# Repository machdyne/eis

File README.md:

# Eis Computer

Eis is a small FPGA computer designed by Lone Dynamics Corporation.

This repo contains schematics, PCB layouts, pinouts, example firmware, gateware, documentation and a 3D printable case.

Find more information on the [Eis product page](https://machdyne.com/product/eis-computer/).

## Blinky 

Building the blinky example requires [Yosys](https://github.com/YosysHQ/yosys), [nextpnr-ice40](https://github.com/YosysHQ/nextpnr) and [IceStorm](https://github.com/YosysHQ/icestorm).

Assuming they are installed, you can simply type `make` to build the gateware, which will be written to output/blinky.bin. You can then connect the USB-C port to your computer and use the latest version of [ldprog](https://github.com/machdyne/ldprog) to write the gateware to the device.

## Programming

The RP2040 firmware, FPGA SRAM and flash MMOD can be programmed over the USB-C port.

Configure the FPGA SRAM:

```
$ ldprog -i -s blinky.bin
```

Program the flash MMOD:

```
$ ldprog -i -f blinky.bin
```

## Firmware

Eis ships with RP2040 [firmware](firmware) based on the [Müsli](https://github.com/machdyne/musli) firmware which allows it to communicate with [ldprog](https://github.com/machdyne/ldprog).

The firmware is responsible for initializing the system, [configuring and outputting the system clock](https://raspberrypi.github.io/pico-sdk-doxygen/group__hardware__clocks.html#details), and either configuring the FPGA or telling the FPGA to configure itself from the MMOD.

The system clock (CLK\_RP) is 48MHz by default.

The firmware can be updated by holding down the BOOTSEL button, connecting the USB-C port to your computer, and then dragging and dropping a new UF2 file to the device filesystem.

The firmware can be built from source or you can use the latest `eis.uf2` binary from the firmware directory.

## SOC

[Zucker](https://github.com/machdyne/zucker) is an experimental RISC-V SOC that supports Eis.

## Pinouts

 * [MMOD](https://github.com/machdyne/mmod)
 * [DDMI](https://github.com/machdyne/ddmi)

## License

The contents of this repo are released under the [Lone Dynamics Open License](LICENSE.md) with the following exceptions:

- The KiCad design files contain parts of the [kicad-pmod](https://github.com/mithro/kicad-pmod) library which is released under the [Apache License, Version 2.0](https://www.apache.org/licenses/LICENSE-2.0.html).

- The KiCad design files may contain symbols and footprints released under other licenses; please contact us if we've failed to give proper attribution.

Note: You can use these designs for commercial purposes but we ask that instead of producing exact clones, that you either replace our trademarks and logos with your own or add your own next to ours.

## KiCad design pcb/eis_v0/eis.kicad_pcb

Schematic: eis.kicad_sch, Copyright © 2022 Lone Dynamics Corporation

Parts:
C1, C43: 1uF; C_0603_1608Metric
C2, C4, C6, C11, C12, C13, C17, C18: 100nF; C_0603_1608Metric
C3, C5, C8, C9: 220nF; C_0603_1608Metric
C7, C16: 4.7uF; C_0603_1608Metric
C10: 10nF; C_0603_1608Metric
C14, C15: 10uF; C_0603_1608Metric
C19, C20, C21, C23: 100nF; R_0603_1608Metric
C22: 1uF; R_0603_1608Metric
C24, C25: 15pF; C_0402_1005Metric
C26, C34, C40: 1uF; C_0402_1005Metric
C27, C28, C29, C30, C31, C32, C33, C35, C36, C39: 100nF; C_0402_1005Metric
C37: 10uF; R_0402_1005Metric
C38: 100nF; R_0402_1005Metric
C41, C42, C44, C46, C47, C48: 22uF; C_0603_1608Metric
C45: 4.7uF; R_0603_1608Metric
D1: D_Schottky_Small; D_0603_1608Metric
D2: LED; LED_0603_1608Metric
FB1, FB2: Ferrite_Bead; R_0603_1608Metric
H1, H2, H3, H4: MountingHole_Pad; MountingHole_3.2mm_M3_Pad
J1: TYPE-C-31-M-12-FIXED; USB_C_Receptacle_HRO_TYPE-C-31-M-12; PARTREV A
J2: USB_A; USB_A_Stewart_SS-52100-001_Horizontal
J3: MICROSD; SDCARD
J4: Conn_01x02_Male; PinHeader_1x02_P2.54mm_Vertical
J5: HDMI_TE_1827059-3-FIXED
L1, L2: 1uH; L_0603_1608Metric
MMOD1: PMOD-Device-x1-Type-2-SPI; PinSocket_1x06_P2.54mm_Horizontal
PMOD1: PMOD-Device-x2-Type-1A-GPIO; PMOD_2x06_HOST
R1, R8: 5K1; R_0603_1608Metric
R2, R3: 27R; R_0402_1005Metric
R4, R5, R18, R19, R20: 20K; R_0402_1005Metric
R6, R7, R9, R16: 10K; R_0402_1005Metric
R10, R11: 100R; R_0603_1608Metric
R12, R13: 22R; R_0402_1005Metric
R14: 536R; R_0603_1608Metric
R15: 1K; R_0402_1005Metric
R17: 1K; R_0603_1608Metric
R21, R22, R23, R24, R25, R26, R27, R28: 270R; R_0402_1005Metric
R29: 210K; R_0603_1608Metric
R30: 47K; R_0603_1608Metric
R31, R32: 200K; R_0603_1608Metric
SW1: BOOT; Button_2P_3x4mm
TP1: TP_PWR5V0; TestPoint_THTPad_D1.0mm_Drill0.5mm
TP2, TP3, TP4, TP5, TP6, TP7, TP8, TP9: TestPoint; TestPoint_Pad_1.0x1.0mm
TP10: TP_PWR1V8; TestPoint_THTPad_D1.0mm_Drill0.5mm
TP11, TP12: TestPoint; TestPoint_THTPad_D1.0mm_Drill0.5mm
U1: ICE40HX4K-BG121; BGA-121_9.0x9.0mm_Layout11x11_P0.8mm_Ball0.4mm_Pad0.35mm_NS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
U2: APS256; APS256_BGA_24
U3: IS61WV256; BGA48C75P8X6_800X600X120N
U4: RP2040; RP2040-QFN-56-OFFICIAL; PARTREV 1.6.1
U5: W25Q32JVSS; SOIC-8_3.9x4.9mm_P1.27mm
U6: NCP164ASN180T1G; TSOP-5_1.65x3.05mm_P0.95mm
U7, U8: AP61300Z6-7; SOT-563
Y1: ECS-80-12-33-JGN-TR-12MHZ; XTAL_ECS-240-8-33-AGN-TR

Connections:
/BOOT: R17.1, SW1.1
/CDONE: R7.1, U1.K8 (CDONE), U4.5 (GPIO3)
/CRESET: R9.1, U1.L9 (~CRESET), U4.4 (GPIO2)
/CSPI_SCK: J3.5 (CLK), MMOD1.3 (MISO), R6.1, U1.L10 (IOB_107_SCK), U4.38 (GPIO26/ADC0)
/CSPI_SI: J3.7 (DAT0), MMOD1.4 (SCK), R5.1, U1.J9 (IOB_106_SDI), U4.39 (GPIO27/ADC1)
/CSPI_SO: J3.3 (CMD), MMOD1.5 (GND), R4.1, U1.K9 (IOB_105_SDO), U4.36 (GPIO24)
/CSPI_SS: MMOD1.6 (VCC), U1.K10 (IOB_108_SS), U4.34 (GPIO22)
/DDMIC_CK_N: J5.12 (CK-), R28.2
/DDMIC_CK_P: J5.10 (CK+), R27.2
/DDMIC_D0_N: J5.9 (D0-), R26.2
/DDMIC_D0_P: J5.7 (D0+), R25.2
/DDMIC_D1_N: J5.6 (D1-), R24.2
/DDMIC_D1_P: J5.4 (D1+), R23.2
/DDMIC_D2_N: J5.3 (D2-), R22.2
/DDMIC_D2_P: J5.1 (D2+), R21.2
/DDMI_CK_N: R28.1, U1.G1 (IOL_14A_GBIN6)
/DDMI_CK_P: R27.1, U1.G2 (IOL_14B)
/DDMI_D0_N: R26.1, U1.H1 (IOL_18A)
/DDMI_D0_P: R25.1, U1.H2 (IOL_18B)
/DDMI_D1_N: R24.1, U1.J1 (IOL_23A)
/DDMI_D1_P: R23.1, U1.J2 (IOL_25B)
/DDMI_D2_N: R22.1, U1.K1 (IOL_23B)
/DDMI_D2_P: R21.1, U1.K2 (IOL_25A)
/HRAM_ADQ0: U1.J11 (IOR_114), U2.D3 (ADQ0)
/HRAM_ADQ1: U1.G10 (IOR_120), U2.D2 (ADQ1)
/HRAM_ADQ2: U1.G9 (IOR_128), U2.C4 (ADQ2)
/HRAM_ADQ3: U1.H10 (IOR_116), U2.D4 (ADQ3)
/HRAM_ADQ4: U1.F9 (IOR_137), U2.D5 (ADQ4)
/HRAM_ADQ5: U1.K11 (IOR_115), U2.E3 (ADQ5)
/HRAM_ADQ6: U1.J10 (IOR_117), U2.E2 (ADQ6)
/HRAM_ADQ7: U1.G11 (IOR_129), U2.E1 (ADQ7)
/HRAM_CE: U1.D10 (IOR_154), U2.A3 (CE#)
/HRAM_CK: U1.E10 (IOR_141_GBIN2), U2.B2 (CK)
/HRAM_DQ8: U1.F10 (IOR_136), U2.C2 (DQ8)
/HRAM_DQ9: U1.E11 (IOR_148), U2.B1 (DQ9)
/HRAM_DQ10: U1.D11 (IOR_152), U2.A2 (DQ10)
/HRAM_DQ11: U1.C11 (IOR_160), U2.A4 (DQ11)
/HRAM_DQ12: U1.B11 (IOR_161), U2.A5 (DQ12)
/HRAM_DQ13: U1.E8 (IOR_146), U2.B4 (DQ13)
/HRAM_DQ14: U1.D9 (IOR_147), U2.B5 (DQ14)
/HRAM_DQ15: U1.H11 (IOR_119), U2.C5 (DQ15)
/HRAM_DQS0: U1.F11 (IOR_140_GBIN3), U2.C3 (DQSDM0)
/HRAM_DQS1: U1.E9 (IOR_144), U2.B3 (DQSDM1)
/LED: R14.1, U1.G3 (IOL_17A)
/PMOD_A1: PMOD1.1 (IOA0), U1.L4 (IOB_72)
/PMOD_A2: PMOD1.2 (IOA1), U1.L1 (IOB_56)
/PMOD_A3: PMOD1.3 (IOA2), U1.K3 (IOB_63)
/PMOD_A4: PMOD1.4 (IOA3), U1.J4 (IOB_64)
/PMOD_A7: PMOD1.7 (IOB0), U1.L3 (IOB_71)
/PMOD_A8: PMOD1.8 (IOB1), U1.K5 (IOB_79)
/PMOD_A9: PMOD1.9 (IOB2), U1.K4 (IOB_73)
/PMOD_A10: PMOD1.10 (IOB3), U1.J3 (IOB_57)
/PWR1V1: C30.1, C32.1, C34.1, U4.23 (DVDD), U4.45 (VREG_VOUT), U4.50 (DVDD)
/PWR1V2: C1.1, C3.1, C5.1, C8.1, C9.1, C10.1, C44.1, C48.1, L2.2, R10.1, R11.1, R31.1, TP12.1, U1.D4 (VCC), U1.D8 (VCC), U1.H4 (VCC), U1.H8 (VCC), U7.5 (EN), U8.6 (OUT)
/PWR1V8: C11.1, C19.2, C20.2, C45.2, TP10.1, U1.F8 (VCCIO_1), U2.D1 (VDD), U2.E4 (VDD1), U6.5 (OUT)
/PWR2V5: C6.1, D1.1 (K), U1.C10 (VPP_2V5)
/PWR3V3: C2.1, C4.1, C17.1, C18.1, C21.2, C22.2, C23.2, C26.1, C27.1, C28.1, C29.1, C31.1, C33.1, C35.1, C36.1, C37.1, C38.1, C39.1, C40.1, C43.1, C46.1, C47.1, D1.2 (A), D2.2 (A), J3.4 (VDD), L1.2, MMOD1.1 (SS), PMOD1.6 (VCC), PMOD1.12 (VCC), R4.2, R5.2, R6.2, R7.2, R9.2, R16.1, R18.1, R19.1, R20.1, R29.1, TP11.1, U1.D6 (VCCIO_0), U1.E4 (VCCIO_3), U1.G4 (VCCIO_3), U1.H6 (VCCIO_2), U1.L11 (VCC_SPI), U3.D6 (VDD2), U3.E1 (VDD1), U4.1 (IOVDD), U4.10 (IOVDD), U4.22 (IOVDD), U4.26 (RUN), U4.33 (IOVDD), U4.42 (IOVDD), U4.43 (ADC_AVDD), U4.44 (VREG_VIN), U4.48 (USB_VDD), U4.49 (IOVDD), U5.8 (VCC), U6.1 (IN), U6.3 (EN), U7.6 (OUT)
/PWR5V0: C7.1, C16.1, C41.1, C42.1, FB1.1, FB2.1, J4.1, J5.18 (+5V), TP1.1, U7.3 (VIN), U8.3 (VIN), U8.5 (EN)
/RP_CLK: U1.L5 (IOB_81_GBIN5), U4.35 (GPIO23)
/RP_INT: U1.K7 (IOB_89), U4.29 (GPIO18)
/RP_QSPI_IO0: TP3.1, U4.53 (QSPI_SD0), U5.5 (DI(IO0))
/RP_QSPI_IO1: TP4.1, U4.55 (QSPI_SD1), U5.2 (DO(IO1))
/RP_QSPI_IO2: TP5.1, U4.54 (QSPI_SD2), U5.3 (IO2)
/RP_QSPI_IO3: TP6.1, U4.51 (QSPI_SD3), U5.7 (IO3)
/RP_QSPI_SCK: TP7.1, U4.52 (QSPI_SCLK), U5.6 (CLK)
/RP_QSPI_SS: R16.2, R17.2, TP2.1, U4.56 (QSPI_CSN), U5.1 (~CS)
/RP_RX: U1.L8 (IOB_103_CBSEL0), U4.28 (GPIO17)
/RP_SS: U1.J7 (IOB_86), U4.37 (GPIO25)
/RP_TX: U1.L7 (IOB_94), U4.27 (GPIO16)
/SD_DAT1: J3.8 (DAT1), R20.2
/SD_DAT2: J3.1 (DAT2), R19.2
/SD_SS: J3.2 (DAT3/CD), R18.2, U1.J8 (IOB_91), U4.7 (GPIO5)
/SRAM_A0: U1.C1 (IOL_5B), U3.A3 (A0)
/SRAM_A1: U1.D1 (IOL_8B), U3.A4 (A1)
/SRAM_A2: U1.E1 (IOL_8A), U3.A5 (A2)
/SRAM_A3: U1.C2 (IOL_5A), U3.B3 (A3)
/SRAM_A4: U1.D2 (IOL_9A), U3.B4 (A4)
/SRAM_A5: U1.C4 (IOL_4A), U3.C3 (A5)
/SRAM_A6: U1.C3 (IOL_4B), U3.C4 (A6)
/SRAM_A7: U1.C7 (IOT_191), U3.D4 (A7)
/SRAM_A8: U1.A7 (IOT_192), U3.H2 (A8)
/SRAM_A9: U1.A8 (IOT_190), U3.H3 (A9)
/SRAM_A10: U1.A9 (IOT_178), U3.H4 (A10)
/SRAM_A11: U1.A10 (IOT_170), U3.H5 (A11)
/SRAM_A12: U1.B7 (IOT_197_GBIN1), U3.G3 (A12)
/SRAM_A13: U1.B8 (IOT_177), U3.G4 (A13)
/SRAM_A14: U1.B6 (IOT_198_GBIN0), U3.F3 (A14)
/SRAM_A15: U1.B9 (IOT_174), U3.F4 (A15)
/SRAM_A16: U1.C8 (IOT_179), U3.E4 (A16)
/SRAM_A17: U1.C9 (IOT_172), U3.D3 (A17)
/SRAM_CS: U1.D3 (IOL_9B), U3.B5 (~CS)
/SRAM_D0: U1.E3 (IOL_10B), U3.B6 (D0)
/SRAM_D1: U1.F1 (IOL_12A), U3.C5 (D1)
/SRAM_D2: U1.F2 (IOL_12B), U3.C6 (D2)
/SRAM_D3: U1.F3 (IOL_13B_GBIN7), U3.D5 (D3)
/SRAM_D4: U1.D7 (IOT_181), U3.E5 (D4)
/SRAM_D5: U1.E2 (IOL_10A), U3.F5 (D5)
/SRAM_D6: U1.A11 (IOT_168), U3.F6 (D6)
/SRAM_D7: U1.F4 (IOL_13A), U3.G6 (D7)
/SRAM_D8: U1.A2 (IOT_222), U3.B1 (D8)
/SRAM_D9: U1.A3 (IOT_223), U3.C1 (D9)
/SRAM_D10: U1.B3 (IOT_221), U3.C2 (D10)
/SRAM_D11: U1.A4 (IOT_211), U3.D2 (D11)
/SRAM_D12: U1.B4 (IOT_219), U3.E2 (D12)
/SRAM_D13: U1.B5 (IOT_208), U3.F2 (D13)
/SRAM_D14: U1.A5 (IOT_207), U3.F1 (D14)
/SRAM_D15: U1.A6 (IOT_206), U3.G1 (D15)
/SRAM_LB: U1.A1 (IOT_225), U3.A1 (~LB)
/SRAM_OE: U1.B1 (IOL_2A), U3.A2 (~OE)
/SRAM_UB: U1.B2 (IOL_2B), U3.B2 (~UB)
/SRAM_WE: U1.D5 (IOT_212), U3.G5 (~WE)
/SWCLK: TP8.1, U4.24 (SWCLK)
/SWD: TP9.1, U4.25 (SWD)
/USB1_CONN_DN: J2.2 (D-), R13.1
/USB1_CONN_DP: J2.3 (D+), R12.1
/USB1_DN: R13.2, U4.41 (GPIO29/ADC3)
/USB1_DP: R12.2, U4.40 (GPIO28/ADC2)
/USB_CONN_DN: J1.A7 (DN1), J1.B7 (DN2), R2.1
/USB_CONN_DP: J1.A6 (DP1), J1.B6 (DP2), R3.1
/USB_DN: R2.2, U4.46 (USB_DM)
/USB_DP: R3.2, U4.47 (USB_DP)
/XIN: C24.2, U4.20 (XIN), Y1.1 (IN/OUT)
/XOUT: R15.2, U4.21 (XOUT)
GND: C1.2, C2.2, C3.2, C4.2, C5.2, C6.2, C7.2, C8.2, C9.2, C10.2, C11.2, C16.2, C17.2, C18.2, C19.1, C20.1, C21.1, C22.1, C23.1, C24.1, C25.2, C26.2, C27.2, C28.2, C29.2, C30.2, C31.2, C32.2, C33.2, C34.2, C35.2, C36.2, C37.2, C38.2, C39.2, C40.2, C41.2, C42.2, C43.2, C44.2, C45.1, C46.2, C47.2, C48.2, H1.1, H2.1, H3.1, H4.1, J1.A1 (GND), J1.A12 (GND), J1.B1 (GND), J1.B12 (GND), J1.S1 (SHIELD), J1.S2 (SHIELD), J1.S3 (SHIELD), J1.S4 (SHIELD), J2.4 (GND), J2.5 (Shield), J3.6 (VSS), J4.2, J5.2 (D2S), J5.5 (D1S), J5.8 (D0S), J5.11 (CKS), J5.17 (GND), J5.S1 (SH), J5.S2 (SH), J5.S3 (SH), J5.S4 (SH), MMOD1.2 (MOSI), PMOD1.5 (GND), PMOD1.11 (GND), R1.2, R8.2, R30.2, R32.2, SW1.2, U1.E5 (GND), U1.E6 (GND), U1.E7 (GND), U1.F5 (GND), U1.F6 (GND), U1.F7 (GND), U1.G5 (GND), U1.G6 (GND), U1.G7 (GND), U1.H5 (GND), U2.C1 (VSS), U2.E5 (VSS1), U3.D1 (VSS1), U3.E6 (VSS2), U4.19 (TESTEN), U4.57 (GND), U5.4 (GND), U6.2 (GND), U7.2 (GND), U8.2 (GND), Y1.2 (GND), Y1.4 (GND)
unnamed: C12.1, C14.1, R10.2, U1.J6 (VCCPLL0)
unnamed: C12.2, C14.2, U1.L6 (GNDPLL0)
unnamed: C13.1, C15.1, R11.2, U1.C6 (VCCPLL1)
unnamed: C13.2, C15.2, U1.C5 (GNDPLL1)
unnamed: C25.1, R15.1, Y1.3 (OUT/IN)
unnamed: D2.1 (K), R14.2
unnamed: FB1.2, J1.A4 (VBUS), J1.A9 (VBUS), J1.B4 (VBUS), J1.B9 (VBUS)
unnamed: FB2.2, J2.1 (VBUS)
unnamed: J1.A5 (CC1), R1.1
unnamed: J1.B5 (CC2), R8.1
unnamed: L1.1, U7.4 (SW)
unnamed: L2.1, U8.4 (SW)
unnamed: R29.2, R30.1, U7.1 (FB)
unnamed: R31.2, R32.1, U8.1 (FB)

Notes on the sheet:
SPI1 RX
CLOCK GPOUT1
UART0 RX
USB1: RP2040 USB HOST (PIO)
0.6V * (1 + (210/47)) = 3.28V
SPI1 CSn
C1=15pF, C2=15pF, CL=12pF, Cstray=5, (C1*C2)/(C1+C2)+Cstray == CL
SPI0 CSn
UART0 TX
0.6V * (1 + (200/200)) = 1.2V
Differential Data Multiple Interface
USB0: POWER / RP2040 CONFIG
SPI0 TX
SPI1 TX
Note: CSPI_SS has 10K pull-up on MMOD module.
SPI0 RX
SPI1 SCK
SPI0 SCK
Eis Computer

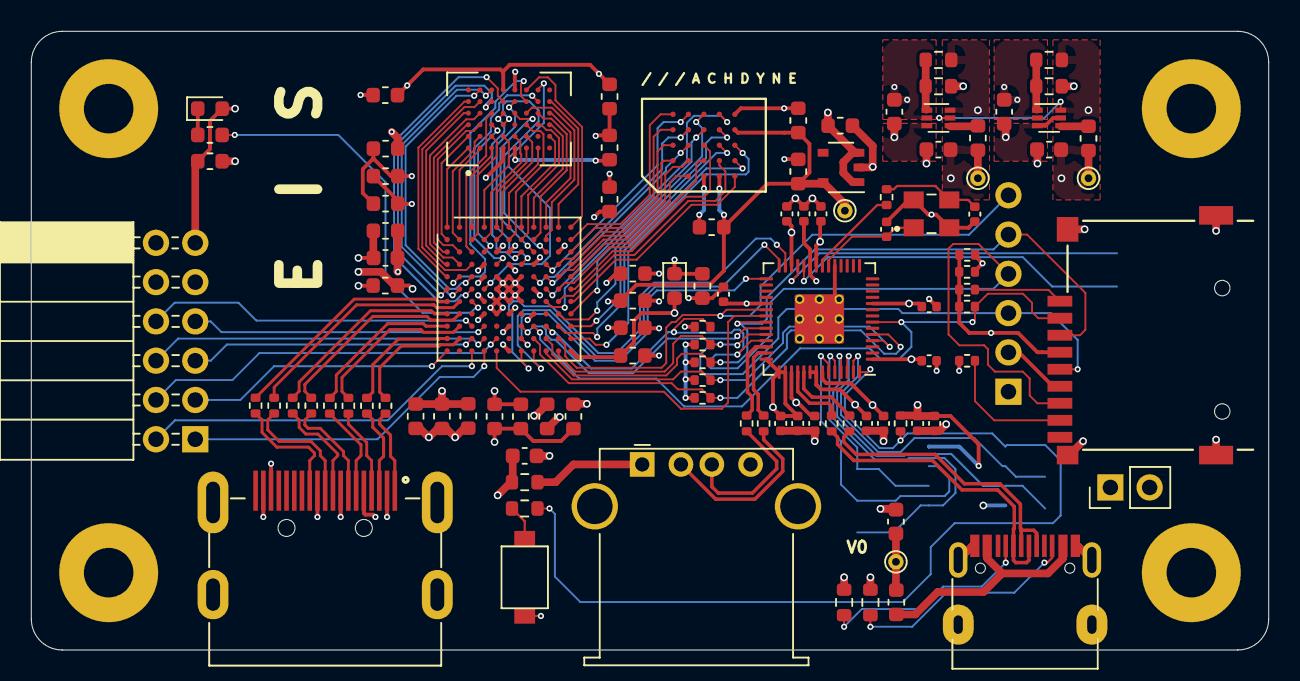
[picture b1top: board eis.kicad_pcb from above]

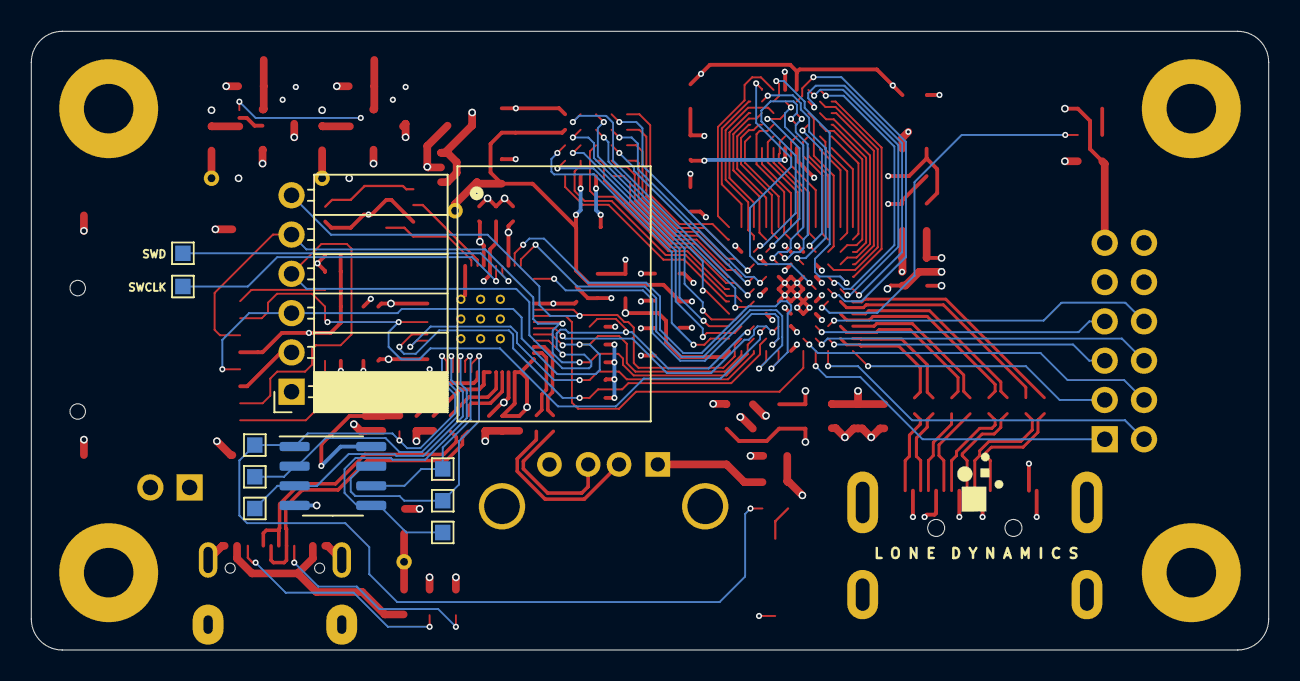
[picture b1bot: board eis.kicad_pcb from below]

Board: 4 copper layers, 80.0 x 40.0 mm, 120 parts (11 on the bottom side), 138 nets.

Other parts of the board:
CONFIG-MMOD: LD-MMOD

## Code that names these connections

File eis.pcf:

# Eis V0
# ------

set_io CLK_48	L5		# this is CLK_RP

set_io LED_A	G3

# PMOD_A
set_io PMOD_A1  L4
set_io PMOD_A2  L1
set_io PMOD_A3  K3
set_io PMOD_A4  J4
set_io PMOD_A7  L3
set_io PMOD_A8  K5
set_io PMOD_A9  K4
set_io PMOD_A10 J3

# UART on PMODA
set_io UART0_RTS  L4
set_io UART0_RX   L1
set_io UART0_TX   K3
set_io UART0_CTS  J4

# --

# DDMI
set_io DDMI_D0_P	H2
set_io DDMI_D0_N	H1
set_io DDMI_D1_P	J2
set_io DDMI_D1_N	J1
set_io DDMI_D2_P	K2
set_io DDMI_D2_N	K1
set_io DDMI_CK_P	G2
set_io DDMI_CK_N	G1

# RP2040
set_io RP_INT		K7
set_io RP_TX		L7
set_io RP_RX		L8

# MMOD/SD SPI BUS
set_io SPI_SS_FLASH  K10
set_io SPI_SS_SD		J8
set_io SPI_SS_RP		J7
set_io SPI_SCK       L10
set_io SPI_MISO      J9		# CSPI_SI
set_io SPI_MOSI      K9		# CSPI_SO

# STATIC RAM
set_io SRAM_A0		C1
set_io SRAM_A1		D1
set_io SRAM_A2		E1
set_io SRAM_A3		C2
set_io SRAM_A4		D2
set_io SRAM_A5		C4
set_io SRAM_A6		C3
set_io SRAM_A7		C7
set_io SRAM_A8		A7
set_io SRAM_A9		A8
set_io SRAM_A10	A9
set_io SRAM_A11	A10
set_io SRAM_A12	B7
set_io SRAM_A13	B8
set_io SRAM_A14	B6
set_io SRAM_A15	B9
set_io SRAM_A16	C8
set_io SRAM_A17	C9

set_io SRAM0_D0		E3
set_io SRAM0_D1		F1
set_io SRAM0_D2		F2
set_io SRAM0_D3		F3
set_io SRAM0_D4		D7
set_io SRAM0_D5		E2
set_io SRAM0_D6		A11
set_io SRAM0_D7		F4
set_io SRAM0_D8		A2
set_io SRAM0_D9		A3
set_io SRAM0_D10	B3
set_io SRAM0_D11	A4
set_io SRAM0_D12	B4
set_io SRAM0_D13	B5
set_io SRAM0_D14	A5
set_io SRAM0_D15	A6

set_io SRAM0_CE		D3
set_io SRAM0_WE		D5
set_io SRAM0_OE		B1
set_io SRAM0_LB		A1
set_io SRAM0_UB		B2

# OPI PSRAM
set_io HRAM_ADQ0	J11
set_io HRAM_ADQ1	G10
set_io HRAM_ADQ2	G9
set_io HRAM_ADQ3	H10
set_io HRAM_ADQ4	F9
set_io HRAM_ADQ5	K11
set_io HRAM_ADQ6	J10
set_io HRAM_ADQ7	G11
set_io HRAM_DQ8	F10
set_io HRAM_DQ9	E11
set_io HRAM_DQ10	D11
set_io HRAM_DQ11	C11
set_io HRAM_DQ12	B11
set_io HRAM_DQ13	E8
set_io HRAM_DQ14	D9
set_io HRAM_DQ15	H11
set_io HRAM_DQS0	F11
set_io HRAM_DQS1	E9
set_io HRAM_CK		E10
set_io HRAM_CE		D10

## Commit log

2022-11-06 add image
2022-11-10 3d printable case
2022-11-10 usb keyboard support
2022-11-10 make keyboard work when using stand-alone power supply
2022-11-15 add firmware binary
2022-11-15 add musli firmware for testing
2022-11-16 remove tinyusb dependency
2022-11-19 support fpga config from microsd
2022-11-19 update firmware image
2023-02-21 add hardware notes
2023-04-25 improve fit
2023-04-26 add pcb
